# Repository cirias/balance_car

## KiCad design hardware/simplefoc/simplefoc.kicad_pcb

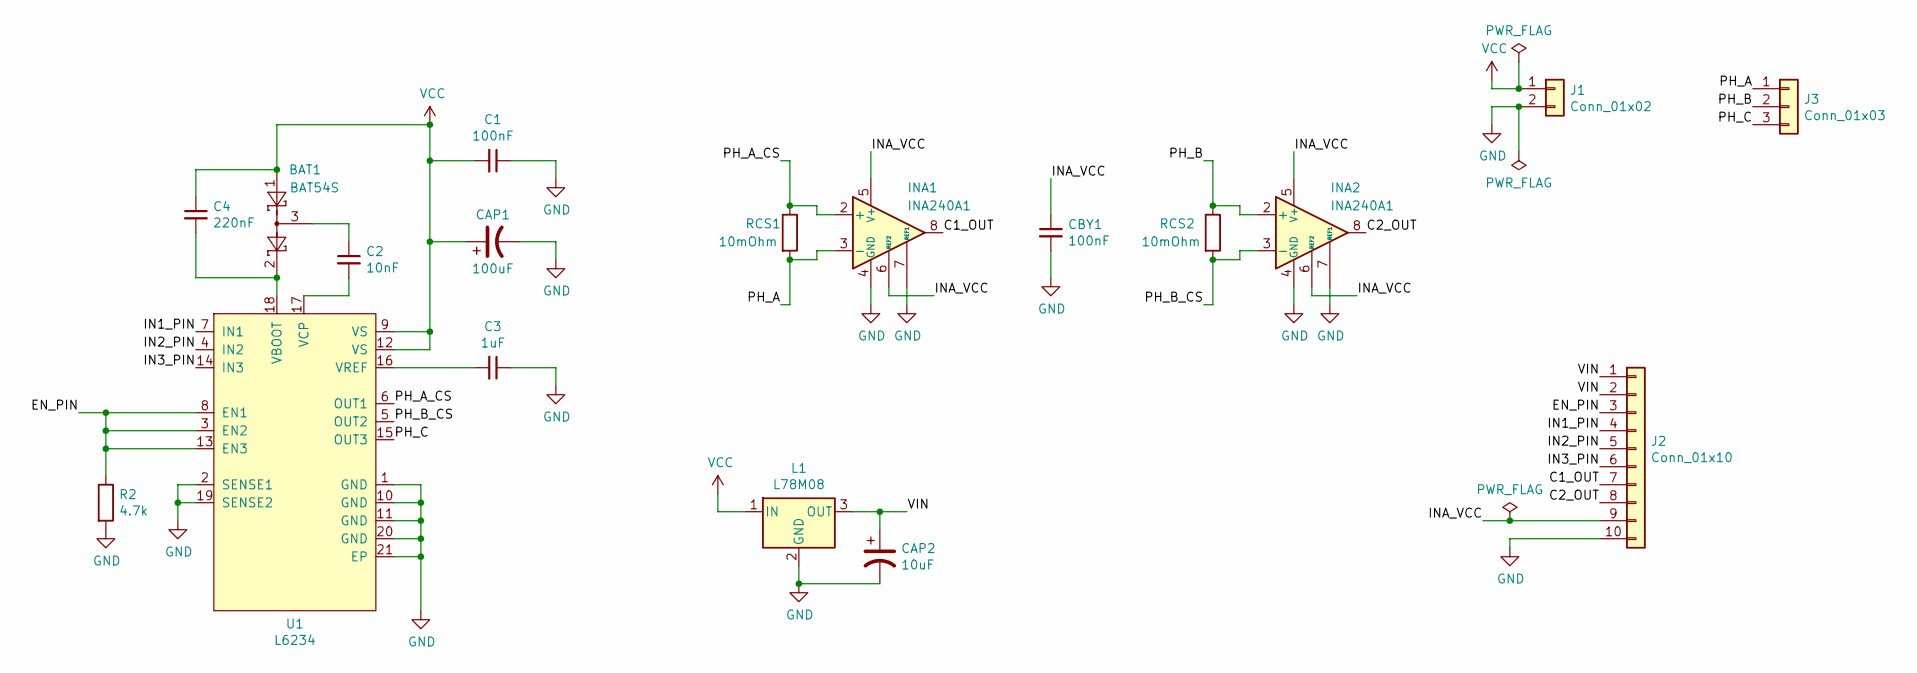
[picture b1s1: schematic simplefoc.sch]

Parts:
BAT1: BAT54S; SOT-23
C1: 100nF; C_1206_3216Metric_Pad1.33x1.80mm_HandSolder; LCSC C24497
C2: 10nF; C_1206_3216Metric_Pad1.33x1.80mm_HandSolder; LCSC C152841
C3: 1uF; C_1206_3216Metric_Pad1.33x1.80mm_HandSolder; LCSC C1848
C4: 220nF; C_1206_3216Metric_Pad1.33x1.80mm_HandSolder; LCSC C1857
CAP1: 100uF; CP_Elec_6.3x7.7; LCSC C127971
CAP2: 10uF; CP_Elec_5x5.4
CBY1: 100nF; C_1206_3216Metric_Pad1.33x1.80mm_HandSolder
INA1, INA2: INA240A1; TSSOP-8_4.4x3mm_P0.65mm
J1: Conn_01x02; Term_Block_1x2_P5mm
J2: Conn_01x10; PinSocket_1x10_P2.54mm_Vertical
J3: Conn_01x03; Term_Block_1x3_P5mm
L1: L78M08; TO-252-2
R2: 4.7k; R_1206_3216Metric_Pad1.30x1.75mm_HandSolder; LCSC C17936
RCS1, RCS2: 10mOhm; R_2512_6332Metric_Pad1.40x3.35mm_HandSolder
U1: L6234; HSOP-20-1EP_11.0x15.9mm_P1.27mm_SlugDown_ThermalVias

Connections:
/C1_OUT: INA1.8, J2.7
/C2_OUT: INA2.8, J2.8
/EN_PIN: J2.3, R2.1, U1.3 (EN2), U1.8 (EN1), U1.13 (EN3)
/IN1_PIN: J2.4, U1.7 (IN1)
/IN2_PIN: J2.5, U1.4 (IN2)
/IN3_PIN: J2.6, U1.14 (IN3)
/INA_VCC: CBY1.1, INA1.5 (V+), INA1.6 (REF2), INA2.5 (V+), INA2.6 (REF2), J2.9
/PH_A: INA1.3 (-), J3.1, RCS1.2
/PH_A_CS: INA1.2 (+), RCS1.1, U1.6 (OUT1)
/PH_B: INA2.2 (+), J3.2, RCS2.1
/PH_B_CS: INA2.3 (-), RCS2.2, U1.5 (OUT2)
/PH_C: J3.3, U1.15 (OUT3)
/VIN: CAP2.1, J2.1, J2.2, L1.3 (OUT)
GND: C1.1, C3.1, CAP1.2, CAP2.2, CBY1.2, INA1.1 (GND), INA1.4 (GND), INA1.7 (REF1), INA2.1 (GND), INA2.4 (GND), INA2.7 (REF1), J1.2, J2.10, L1.2 (GND), R2.2, U1.1 (GND), U1.2 (SENSE1), U1.10 (GND), U1.11 (GND), U1.19 (SENSE2), U1.20 (GND), U1.21 (EP)
unnamed: BAT1.2, C4.2, U1.18 (VBOOT)
unnamed: BAT1.3, C2.1
unnamed: C2.2, U1.17 (VCP)
unnamed: C3.2, U1.16 (VREF)
VCC: BAT1.1, C1.2, C4.1, CAP1.1, J1.1, L1.1 (IN), U1.9 (VS), U1.12 (VS)

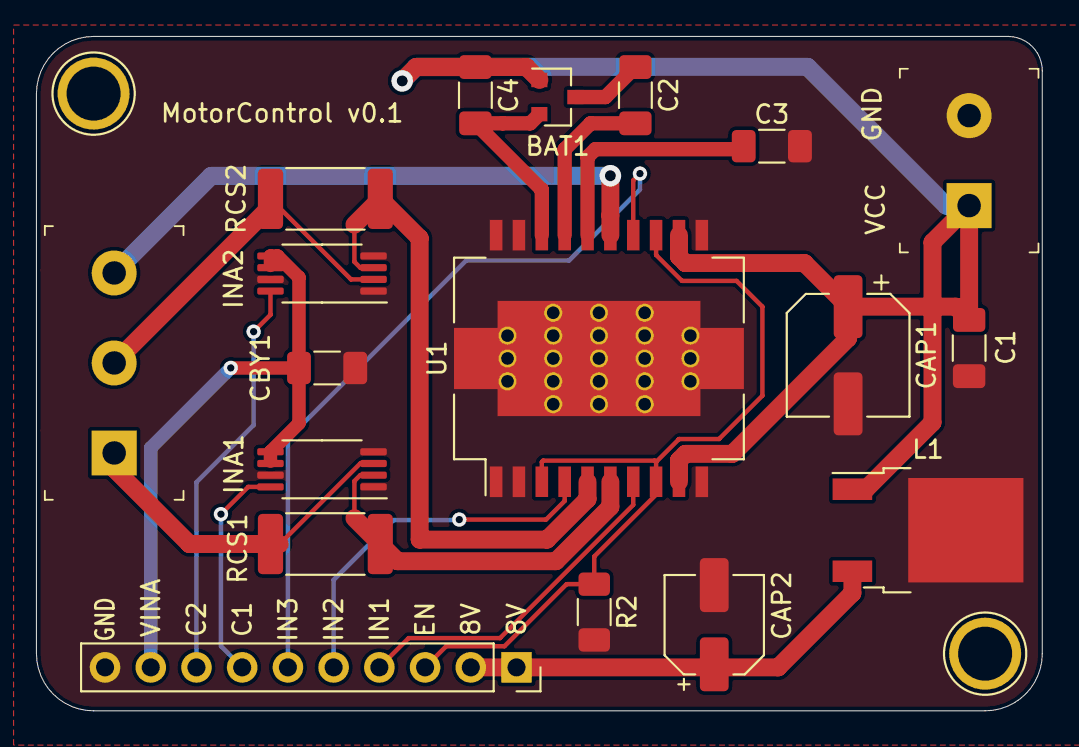
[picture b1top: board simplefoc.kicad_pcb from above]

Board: 2 copper layers, 55.9 x 37.5 mm, 18 parts (0 on the bottom side), 19 nets.

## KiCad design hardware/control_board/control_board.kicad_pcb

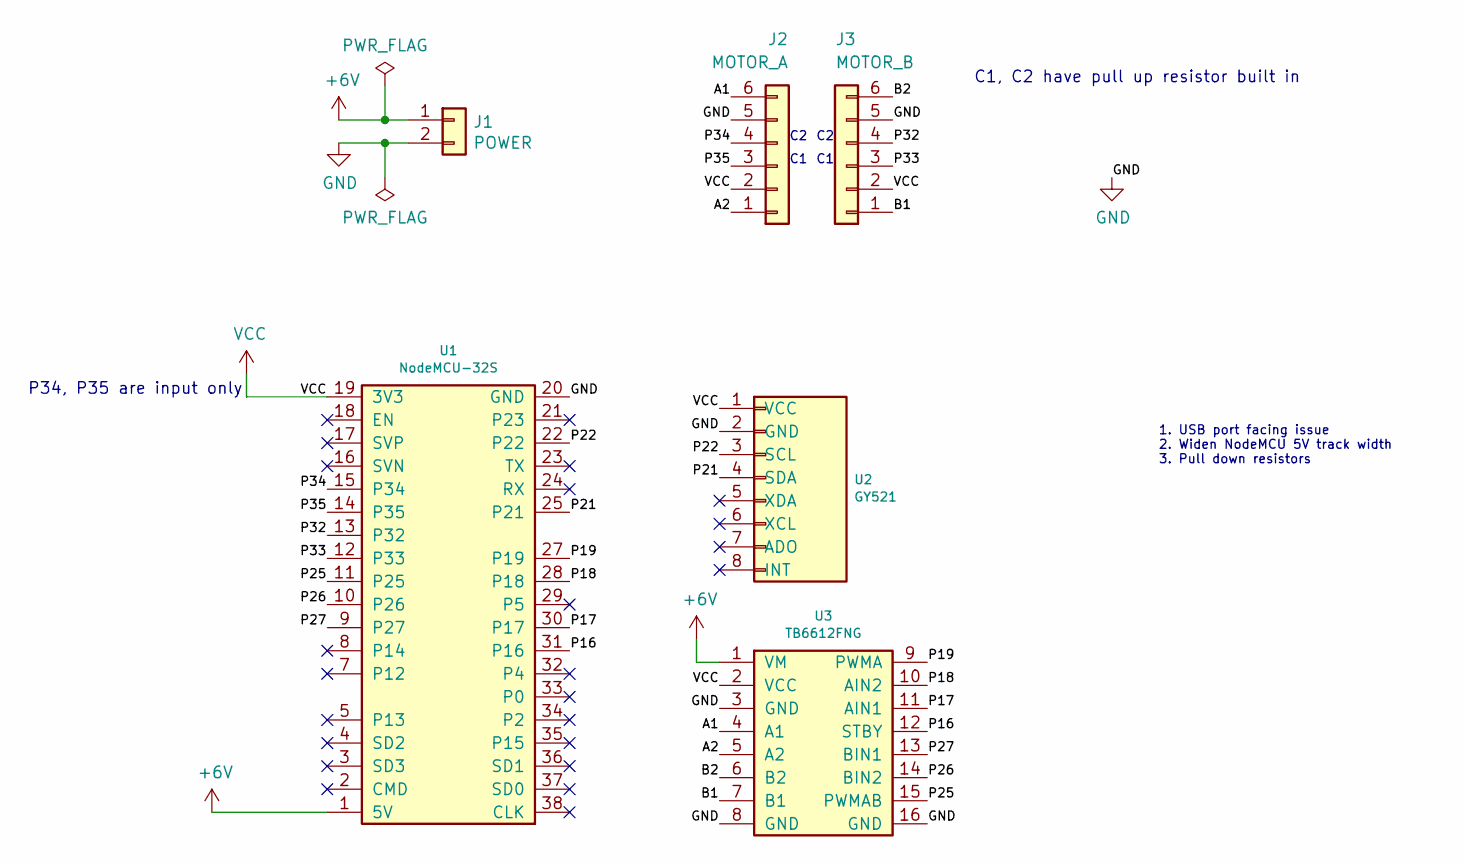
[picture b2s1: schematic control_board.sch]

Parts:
J1: POWER; JST_VH_B2PS-VH_1x02_P3.96mm_Horizontal
J2: MOTOR_A; JST_XH_B6B-XH-A_1x06_P2.50mm_Vertical
J3: MOTOR_B; JST_XH_B6B-XH-A_1x06_P2.50mm_Vertical
U1: NodeMCU-32S; NodeMCU-32S_20Pins
U2: GY521
U3: TB6612FNG

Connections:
+6V: J1.1, U1.1 (5V), U3.1 (VM)
/A1: J2.6, U3.4 (A1)
/A2: J2.1, U3.5 (A2)
/B1: J3.1, U3.7 (B1)
/B2: J3.6, U3.6 (B2)
/P16: U1.31 (P16), U3.12 (STBY)
/P17: U1.30 (P17), U3.11 (AIN1)
/P18: U1.28 (P18), U3.10 (AIN2)
/P19: U1.27 (P19), U3.9 (PWMA)
/P21: U1.25 (P21), U2.4 (SDA)
/P22: U1.22, U2.3 (SCL)
/P25: U1.11 (P25), U3.15 (PWMAB)
/P26: U1.10 (P26), U3.14 (BIN2)
/P27: U1.9 (P27), U3.13 (BIN1)
/P32: J3.4, U1.13 (P32)
/P33: J3.3, U1.12 (P33)
/P34: J2.4, U1.15 (P34)
/P35: J2.3, U1.14 (P35)
GND: J1.2, J2.5, J3.5, U1.20 (GND), U2.2 (GND), U3.3 (GND), U3.8 (GND), U3.16 (GND)
VCC: J2.2, J3.2, U1.19 (3V3), U2.1 (VCC), U3.2 (VCC)

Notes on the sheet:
C1, C2 have pull up resistor built in
P34, P35 are input only
1. USB port facing issue 2. Widen NodeMCU 5V track width 3. Pull down resistors

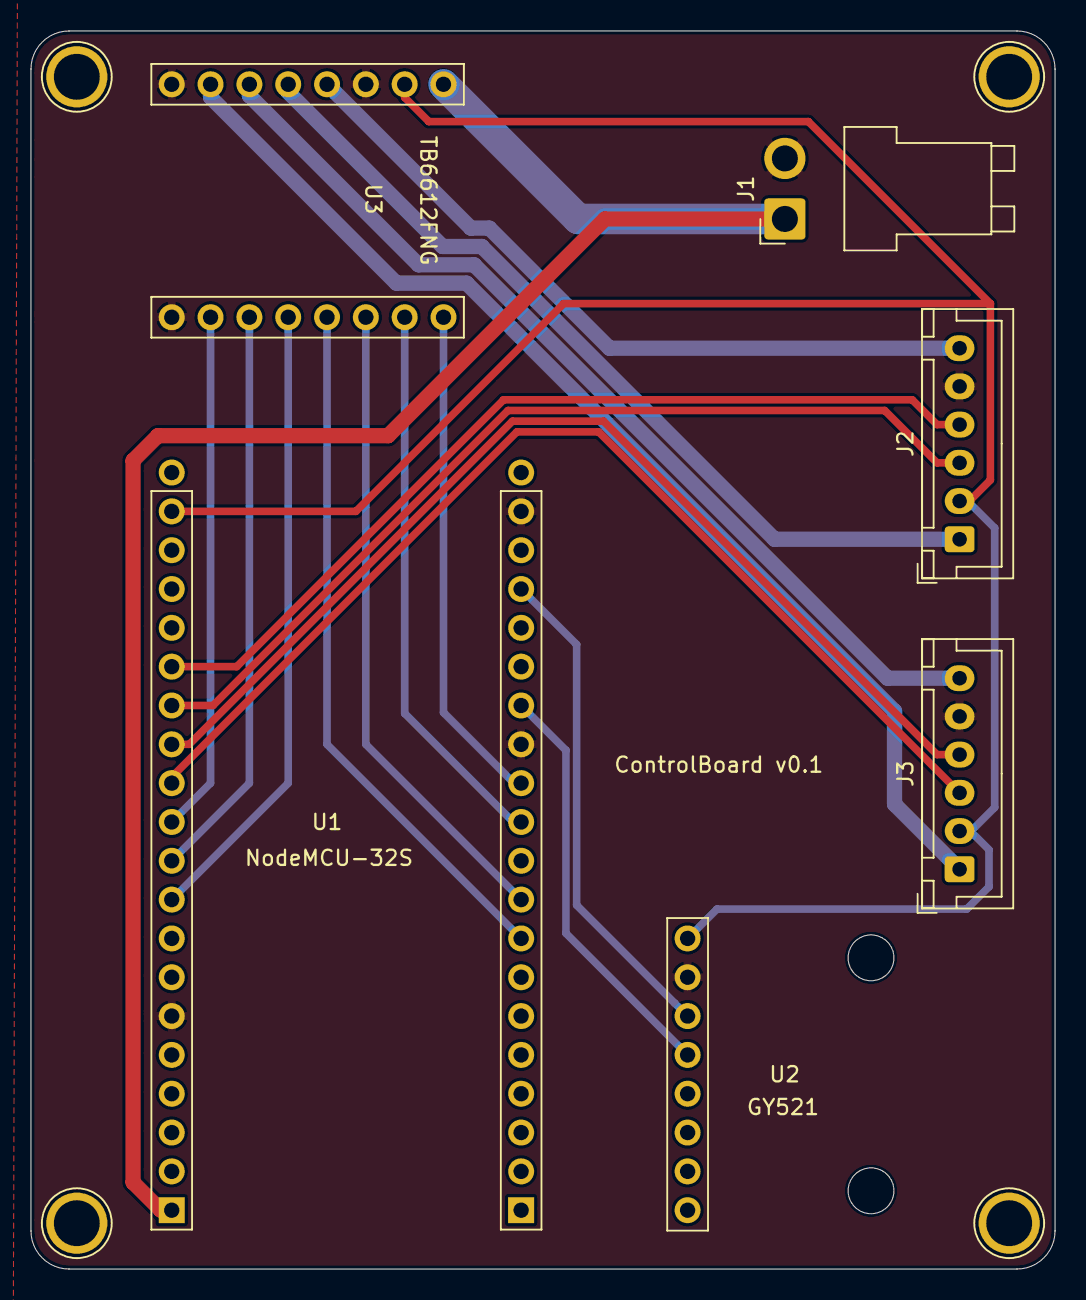
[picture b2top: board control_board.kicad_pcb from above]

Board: 2 copper layers, 67.0 x 81.0 mm, 6 parts (0 on the bottom side), 20 nets.

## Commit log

2021-06-15 Add android app
2021-07-01 Submit files for V2
